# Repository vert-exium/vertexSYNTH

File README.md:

# vertexSYNTH
A custom polyphonic synth made out of aluminum, acrylic, and PETG
See the [journal](docs/JOURNAL.md) for progress!

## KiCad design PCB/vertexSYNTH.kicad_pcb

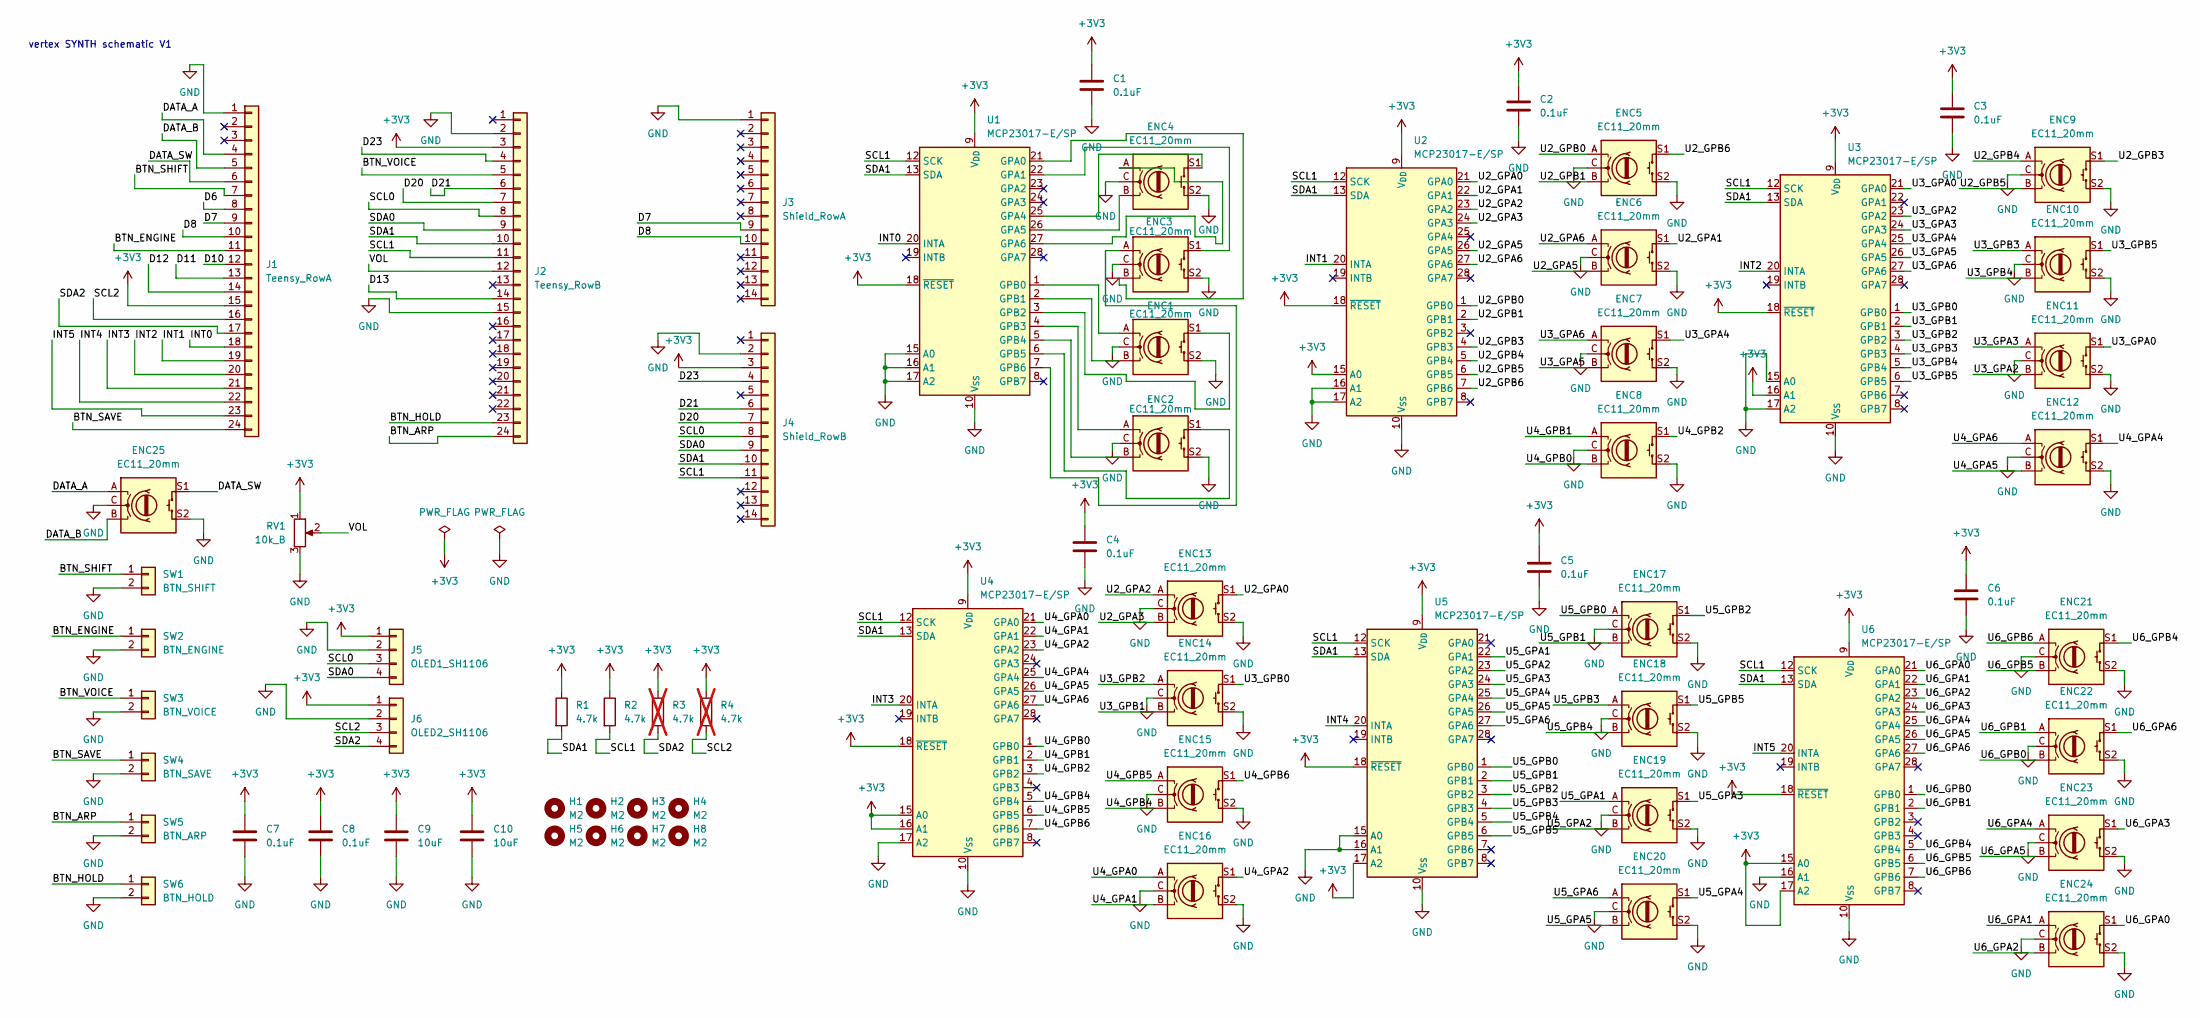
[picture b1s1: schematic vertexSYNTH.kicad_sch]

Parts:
C1, C2, C3, C4, C5, C6, C7, C8: 0.1uF; C_Disc_D3.0mm_W1.6mm_P2.50mm
C9, C10: 10uF; C_Disc_D3.0mm_W1.6mm_P2.50mm
ENC1, ENC2, ENC3, ENC4, ENC5, ENC6, ENC7, ENC8, ENC9, ENC10, ENC11, ENC12, ENC13, ENC14, ENC15, ENC16, ENC17, ENC18, ENC19, ENC20, ENC21, ENC22, ENC23, ENC24, ENC25: EC11_20mm; EC11E_centered
H1, H2, H3, H4, H5, H6, H7, H8: M2; MountingHole_2.2mm_M2
J1: Teensy_RowA; PinSocket_1x24_P2.54mm_Vertical
J2: Teensy_RowB; PinSocket_1x24_P2.54mm_Vertical
J3: Shield_RowA; PinSocket_1x14_P2.54mm_Vertical
J4: Shield_RowB; PinSocket_1x14_P2.54mm_Vertical
J5: OLED1_SH1106; PinHeader_1x04_P2.54mm_Vertical
J6: OLED2_SH1106; PinHeader_1x04_P2.54mm_Vertical
R1, R2: 4.7k; R_Axial_DIN0309_L9.0mm_D3.2mm_P2.54mm_Vertical
R3, R4: 4.7k; R_Axial_DIN0309_L9.0mm_D3.2mm_P2.54mm_Vertical; not fitted
RV1: 10k_B; RK09K_centered
SW1: BTN_SHIFT; PinHeader_1x02_P2.54mm_Vertical
SW2: BTN_ENGINE; PinHeader_1x02_P2.54mm_Vertical
SW3: BTN_VOICE; PinHeader_1x02_P2.54mm_Vertical
SW4: BTN_SAVE; PinHeader_1x02_P2.54mm_Vertical
SW5: BTN_ARP; PinHeader_1x02_P2.54mm_Vertical
SW6: BTN_HOLD; PinHeader_1x02_P2.54mm_Vertical
U1, U2, U3, U4, U5, U6: MCP23017-E/SP; DIP-28_W7.62mm_Socket

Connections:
+3V3: C1.1, C2.1, C3.1, C4.1, C5.1, C6.1, C7.1, C8.1, C9.1, C10.1, J1.15, J2.3, J4.3, J5.1, J6.1, R1.1, R2.1, R3.1, R4.1, RV1.1, U1.9 (V_{DD}), U1.18 (~RESET), U2.9 (V_{DD}), U2.15 (A0), U2.18 (~RESET), U3.9 (V_{DD}), U3.16 (A1), U3.18 (~RESET), U4.9 (V_{DD}), U4.15 (A0), U4.16 (A1), U4.18 (~RESET), U5.9 (V_{DD}), U5.17 (A2), U5.18 (~RESET), U6.9 (V_{DD}), U6.15 (A0), U6.17 (A2), U6.18 (~RESET)
/BTN_ARP: J2.24, SW5.1
/BTN_ENGINE: J1.11, SW2.1
/BTN_HOLD: J2.23, SW6.1
/BTN_SAVE: J1.24, SW4.1
/BTN_SHIFT: J1.7, SW1.1
/BTN_VOICE: J2.5, SW3.1
/D6: J1.8
/D7: J1.9, J3.9
/D8: J1.10, J3.10
/D10: J1.12
/D11: J1.13
/D12: J1.14
/D13: J2.14
/D20: J2.7, J4.7
/D21: J2.6, J4.6
/D23: J2.4, J4.4
/DATA_A: ENC25.A, J1.4
/DATA_B: ENC25.B, J1.5
/DATA_SW: ENC25.S1, J1.6
/INT0: J1.18, U1.20 (INTA)
/INT1: J1.19, U2.20 (INTA)
/INT2: J1.20, U3.20 (INTA)
/INT3: J1.21, U4.20 (INTA)
/INT4: J1.22, U5.20 (INTA)
/INT5: J1.23, U6.20 (INTA)
/SCL0: J2.8, J4.8, J5.3
/SCL1: J2.11, J4.11, R2.2, U1.12 (SCK), U2.12 (SCK), U3.12 (SCK), U4.12 (SCK), U5.12 (SCK), U6.12 (SCK)
/SCL2: J1.16, J6.3, R4.2
/SDA0: J2.9, J4.9, J5.4
/SDA1: J2.10, J4.10, R1.2, U1.13 (SDA), U2.13 (SDA), U3.13 (SDA), U4.13 (SDA), U5.13 (SDA), U6.13 (SDA)
/SDA2: J1.17, J6.4, R3.2
/U2_GPA0: ENC13.S1, U2.21 (GPA0)
/U2_GPA1: ENC6.S1, U2.22 (GPA1)
/U2_GPA2: ENC13.A, U2.23 (GPA2)
/U2_GPA3: ENC13.B, U2.24 (GPA3)
/U2_GPA5: ENC6.B, U2.26 (GPA5)
/U2_GPA6: ENC6.A, U2.27 (GPA6)
/U2_GPB0: ENC5.A, U2.1 (GPB0)
/U2_GPB1: ENC5.B, U2.2 (GPB1)
/U2_GPB3: ENC9.S1, U2.4 (GPB3)
/U2_GPB4: ENC9.A, U2.5 (GPB4)
/U2_GPB5: ENC9.B, U2.6 (GPB5)
/U2_GPB6: ENC5.S1, U2.7 (GPB6)
/U3_GPA0: ENC11.S1, U3.21 (GPA0)
/U3_GPA2: ENC11.B, U3.23 (GPA2)
/U3_GPA3: ENC11.A, U3.24 (GPA3)
/U3_GPA4: ENC7.S1, U3.25 (GPA4)
/U3_GPA5: ENC7.B, U3.26 (GPA5)
/U3_GPA6: ENC7.A, U3.27 (GPA6)
/U3_GPB0: ENC14.S1, U3.1 (GPB0)
/U3_GPB1: ENC14.B, U3.2 (GPB1)
/U3_GPB2: ENC14.A, U3.3 (GPB2)
/U3_GPB3: ENC10.A, U3.4 (GPB3)
/U3_GPB4: ENC10.B, U3.5 (GPB4)
/U3_GPB5: ENC10.S1, U3.6 (GPB5)
/U4_GPA0: ENC16.A, U4.21 (GPA0)
/U4_GPA1: ENC16.B, U4.22 (GPA1)
/U4_GPA2: ENC16.S1, U4.23 (GPA2)
/U4_GPA4: ENC12.S1, U4.25 (GPA4)
/U4_GPA5: ENC12.B, U4.26 (GPA5)
/U4_GPA6: ENC12.A, U4.27 (GPA6)
/U4_GPB0: ENC8.B, U4.1 (GPB0)
/U4_GPB1: ENC8.A, U4.2 (GPB1)
/U4_GPB2: ENC8.S1, U4.3 (GPB2)
/U4_GPB4: ENC15.B, U4.5 (GPB4)
/U4_GPB5: ENC15.A, U4.6 (GPB5)
/U4_GPB6: ENC15.S1, U4.7 (GPB6)
/U5_GPA1: ENC19.A, U5.22 (GPA1)
/U5_GPA2: ENC19.B, U5.23 (GPA2)
/U5_GPA3: ENC19.S1, U5.24 (GPA3)
/U5_GPA4: ENC20.S1, U5.25 (GPA4)
/U5_GPA5: ENC20.B, U5.26 (GPA5)
/U5_GPA6: ENC20.A, U5.27 (GPA6)
/U5_GPB0: ENC17.A, U5.1 (GPB0)
/U5_GPB1: ENC17.B, U5.2 (GPB1)
/U5_GPB2: ENC17.S1, U5.3 (GPB2)
/U5_GPB3: ENC18.A, U5.4 (GPB3)
/U5_GPB4: ENC18.B, U5.5 (GPB4)
/U5_GPB5: ENC18.S1, U5.6 (GPB5)
/U6_GPA0: ENC24.S1, U6.21 (GPA0)
/U6_GPA1: ENC24.A, U6.22 (GPA1)
/U6_GPA2: ENC24.B, U6.23 (GPA2)
/U6_GPA3: ENC23.S1, U6.24 (GPA3)
/U6_GPA4: ENC23.A, U6.25 (GPA4)
/U6_GPA5: ENC23.B, U6.26 (GPA5)
/U6_GPA6: ENC22.S1, U6.27 (GPA6)
/U6_GPB0: ENC22.B, U6.1 (GPB0)
/U6_GPB1: ENC22.A, U6.2 (GPB1)
/U6_GPB4: ENC21.S1, U6.5 (GPB4)
/U6_GPB5: ENC21.B, U6.6 (GPB5)
/U6_GPB6: ENC21.A, U6.7 (GPB6)
/VOL: J2.12, RV1.2
GND: C1.2, C2.2, C3.2, C4.2, C5.2, C6.2, C7.2, C8.2, C9.2, C10.2, ENC1.C, ENC1.S2, ENC2.C, ENC2.S2, ENC3.C, ENC3.S2, ENC4.C, ENC4.S2, ENC5.C, ENC5.S2, ENC6.C, ENC6.S2, ENC7.C, ENC7.S2, ENC8.C, ENC8.S2, ENC9.C, ENC9.S2, ENC10.C, ENC10.S2, ENC11.C, ENC11.S2, ENC12.C, ENC12.S2, ENC13.C, ENC13.S2, ENC14.C, ENC14.S2, ENC15.C, ENC15.S2, ENC16.C, ENC16.S2, ENC17.C, ENC17.S2, ENC18.C, ENC18.S2, ENC19.C, ENC19.S2, ENC20.C, ENC20.S2, ENC21.C, ENC21.S2, ENC22.C, ENC22.S2, ENC23.C, ENC23.S2, ENC24.C, ENC24.S2, ENC25.C, ENC25.S2, J1.1, J2.2, J2.15, J3.1, J4.2, J5.2, J6.2, RV1.3, SW1.2, SW2.2, SW3.2, SW4.2, SW5.2, SW6.2, U1.10 (V_{SS}), U1.15 (A0), U1.16 (A1), U1.17 (A2), U2.10 (V_{SS}), U2.16 (A1), U2.17 (A2), U3.10 (V_{SS}), U3.15 (A0), U3.17 (A2), U4.10 (V_{SS}), U4.17 (A2), U5.10 (V_{SS}), U5.15 (A0), U5.16 (A1), U6.10 (V_{SS}), U6.16 (A1)
unnamed: ENC3.B, U1.21 (GPA0)
unnamed: ENC3.S1, U1.22 (GPA1)
unnamed: ENC4.S1, U1.25 (GPA4)
unnamed: ENC4.B, U1.26 (GPA5)
unnamed: ENC4.A, U1.27 (GPA6)
unnamed: ENC1.A, U1.1 (GPB0)
unnamed: ENC1.B, U1.2 (GPB1)
unnamed: ENC1.S1, U1.3 (GPB2)
unnamed: ENC2.A, U1.4 (GPB3)
unnamed: ENC2.B, U1.5 (GPB4)
unnamed: ENC2.S1, U1.6 (GPB5)
unnamed: ENC3.A, U1.7 (GPB6)

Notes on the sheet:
vertex SYNTH schematic V1

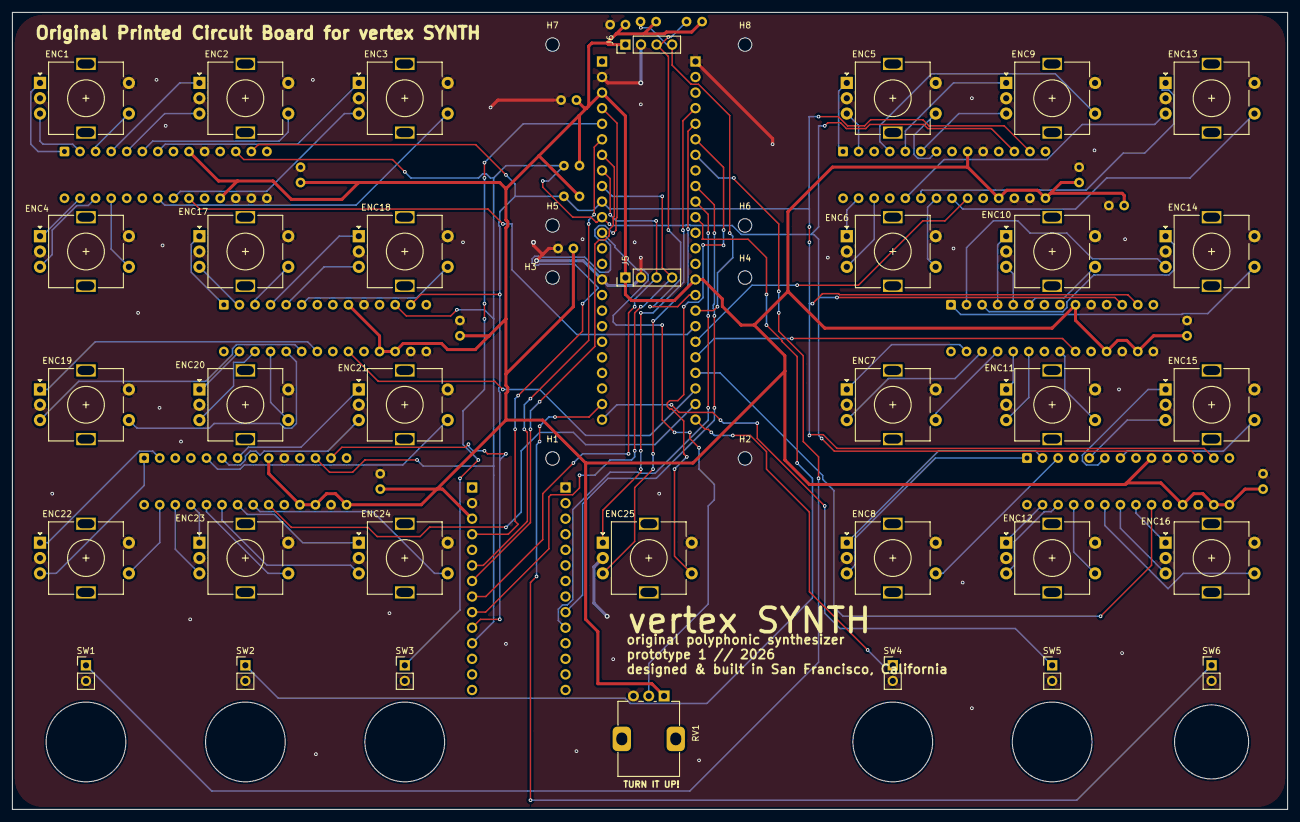
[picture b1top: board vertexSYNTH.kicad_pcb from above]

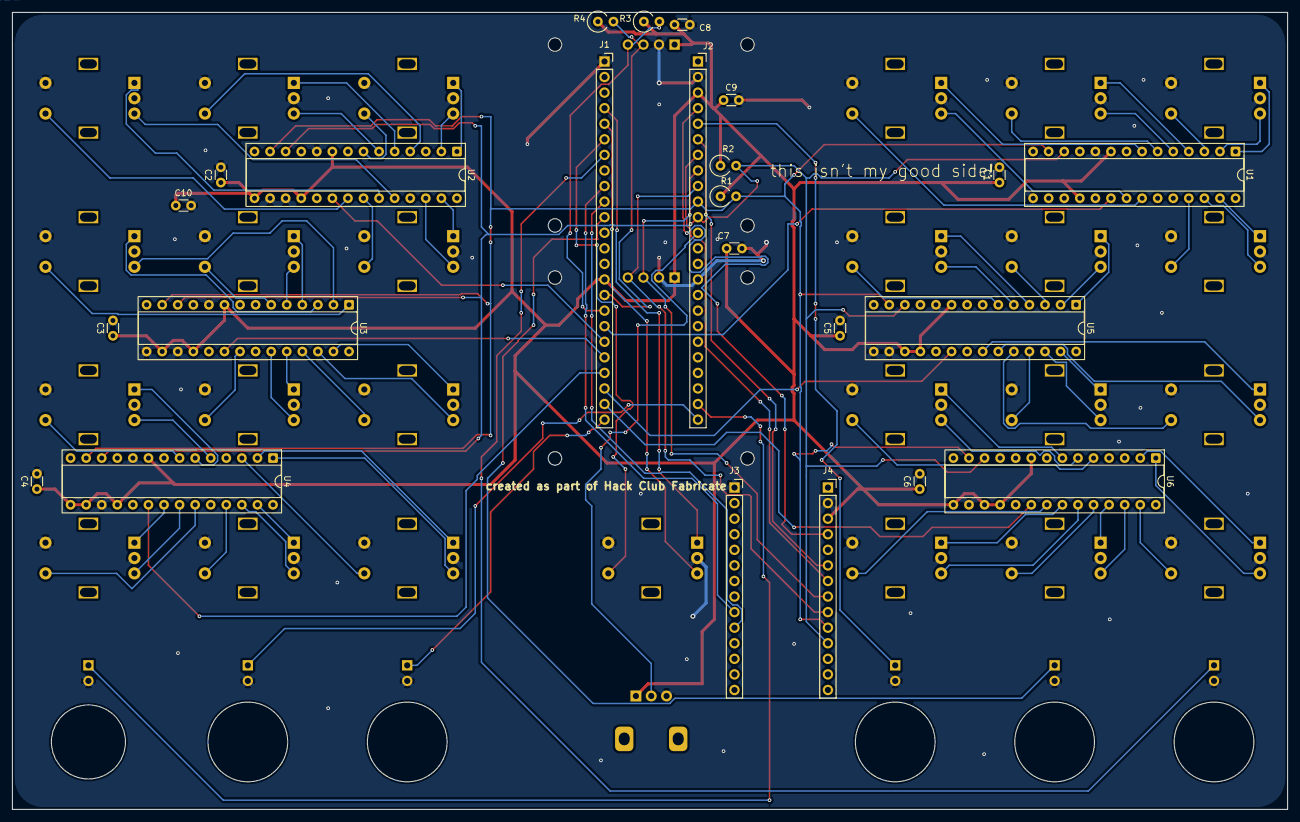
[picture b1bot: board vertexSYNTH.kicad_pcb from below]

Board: 2 copper layers, 208.0 x 130.0 mm, 66 parts (24 on the bottom side), 101 nets.

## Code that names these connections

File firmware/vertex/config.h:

// All wiring info is in this script

#pragma once
#include <Arduino.h>

// Pins wired directly to the Teensy:
const uint8_t PIN_DATA_A = 2;
const uint8_t PIN_DATA_B = 3;
const uint8_t PIN_DATA_SW = 4;

// The six buttons:

const uint8_t NUM_BUTTONS = 6;
enum ButtonId : uint8_t { BTN_SHIFT, BTN_ENGINE, BTN_VOICE, BTN_SAVE, BTN_ARP, BTN_HOLD };
const uint8_t BUTTON_PINS[NUM_BUTTONS] = { 5, 9, 22, 32, 33, 34 };
const char* const BUTTON_NAMES[NUM_BUTTONS] = { "SHIFT", "ENGINE", "VOICE", "SAVE", "ARP", "HOLD" };

// Pin for the volume pot
const uint8_t PIN_VOLUME = 15;
// Whether the volume knob's direction is reversed
const bool VOLUME_POT_REVERSED = false;


// I2C buses 
const uint32_t MCP_I2C_CLOCK = 400000; // setting the clock high so things respond fast
const uint32_t OLED_I2C_CLOCK = 400000;
const uint8_t OLED_I2C_ADDRESS = 0x3C; 

// MCP23017 port expanders

const uint8_t NUM_MCP = 6;
const uint8_t MCP_ADDRESS[NUM_MCP] = { 0x20, 0x21, 0x22, 0x23, 0x24, 0x25 }; // U1-U6
const uint8_t MCP_INT_PIN[NUM_MCP] = { 26, 27, 28, 29, 30, 31 }; // INT0-INT5
const char* const MCP_NAMES[NUM_MPC] = { "U1", "U2", "U3", "U4", "U5", "U6" };

// Sets each chip to be read every millisecond if false, slower but it works
// without any INT lines so it's good for debug
const bool USE_MCP_INT_PINS = true;

// Which encoder is wired to which MCP pin
// GPA0-GPA7 is 0-7, GPB0-GPB7 is 8-15

#define GPA(n) (n)
#define GPB(n) (8 + (n))

struct EncoderWiring {
  uint8_t chip;  // 0 = U1-5 = U6
  uint8_t pinA;  // encoder pin A
  uint8_t pinB;  // encoder pin B
  uint8_t pinSW; // push switch
  const char* ref; // the reference on the PCB
};

// Knob # go in the physical order they're on the PCB, so it's read left block
// top left to left block bottom right and then same for the right block (the other half)
const uint8_t NUM_KNOBS = 24;
const EncoderWiring KNOB_WIRING[NUM_KNOBS] = {
  // chip (1-6), A, B, SW, PCB ref
  {   0, GPB(0),  GPB(1),  GPB(2),  "ENC1"  },
  {   0, GPB(3),  GPB(4),  GPB(5),  "ENC2"  },
  {   0, GPB(6),  GPA(0),  GPA(1),  "ENC3"  },
  {   0, GPA(6),  GPA(5),  GPA(4),  "ENC4"  },
  {   4, GPB(0),  GPB(1),  GPB(2),  "ENC17" },
  {   4, GPB(3),  GPB(4),  GPB(5),  "ENC18" },
  {   4, GPA(1),  GPA(2),  GPA(3),  "ENC19" },
  {   4, GPA(6),  GPA(5),  GPA(4),  "ENC20" },
  {   5, GPB(6),  GPB(5),  GPB(4),  "ENC21" },
  {   5, GPB(1),  GPB(0),  GPA(6),  "ENC22" },
  {   5, GPA(4),  GPA(5),  GPA(3),  "ENC23" },
  {   5, GPA(1),  GPA(2),  GPA(0),  "ENC24" },
  {   1, GPB(0),  GPB(1),  GPB(6),  "ENC5"  },
  {   1, GPB(4),  GPB(5),  GPB(3),  "ENC9"  },
  {   1, GPA(2),  GPA(3),  GPA(0),  "ENC13" },
  {   1, GPA(6),  GPA(5),  GPA(1),  "ENC6"  },
  {   2, GPB(3),  GPB(4),  GPB(5),  "ENC10" },
  {   2, GPB(2),  GPB(1),  GPB(0),  "ENC14" },
  {   2, GPA(6),  GPA(5),  GPA(4),  "ENC7"  },
  {   2, GPA(3),  GPA(2),  GPA(0),  "ENC11" },
  {   3, GPB(5),  GPB(4),  GPB(6),  "ENC15" },
  {   3, GPB(1),  GPB(0),  GPB(2),  "ENC8"  },
  {   3, GPA(6),  GPA(5),  GPA(4),  "ENC12" },
  {   3, GPA(0),  GPA(1),  GPA(2),  "ENC16" },
};

// How many clicks of signal per detend/click
// 4 = one full cycle per detend (EC11 with 20 detents / 20 pulses)
// 2 = half a cycle (for EC11s with 30 detents / 15 pulses)
// Change this if the EC11 isn't acting correctly
const uint8_t ENCODER_STEPS_PER_DETENT = 4;

// flips ALL encoders
const bool KNOBS_REVERSED = false;
// flip the DATA encoder only
const bool DATA_ENCODER_REVERSED = false;

// Screens

// If a screen appears upside down, change to true
const bool OLED_TOP_ROTATE_180 = false; // OLED 2 or J6
const bool OLED_BOTTOM_ROTATE_180 = false; // OLED 1 or J5

// Audio

const uint8_t NUM_VOICES = 6;  // max number of voices
const float HEADPHONE_VOLUME = 0.6f; // audio shield headphone amp (0.0 - 0.8)
const uint8_t LINE_OUT_LEVEL = 21;  // 13 = loudest, 31 = most quiet
// Audio memory blocks, for delay and voices, each one ~260 bytes
const int AUDIO_MEMORY_BLOCKS = 450;
